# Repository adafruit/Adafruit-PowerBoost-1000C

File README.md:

## Adafruit PowerBoost 1000C
<a href="http://www.adafruit.com/products/2465"><br/>
Click here to purchase one from the Adafruit shop</a>

PowerBoost 1000C is the perfect power supply for your portable project! With a built-in load-sharing battery charger circuit, you'll be able to keep your power-hungry project running even while recharging the battery! This little DC/DC boost converter module can be powered by any 3.7V LiIon/LiPoly battery, and convert the battery output to 5.2V DC for running your 5V projects.

If you dont need the 1A battery charger, smart load-sharing, or 1A iOS resistors, check out the Powerboost 500C

Like our popular 5V 1A USB wall adapter, we tweaked the output to be 5.2V instead of a straight-up 5.0V so that there's a little bit of 'headroom' for long cables, high draw, the addition of a diode on the output if you wish, etc. The 5.2V is safe for all 5V-powered electronics like Arduino, Raspberry Pi, or Beagle Bone while preventing icky brown-outs during high current draw because of USB cable resistance.

The PowerBoost 1000C has at the heart a TPS61090 boost converter from TI. This boost converter chip has some really nice extras such as low battery detection, 2A internal switch, synchronous conversion, excellent efficiency, and 700KHz high-frequency operation. 

PCB files for Adafruit PowerBoost 1000C
-  https://www.adafruit.com/product/2465

### License

Adafruit invests time and resources providing this open source design, please support Adafruit and open-source hardware by purchasing products from [Adafruit](https://www.adafruit.com)!

All text above must be included in any redistribution

Designed by Limor Fried/Ladyada for Adafruit Industries.
Creative Commons Attribution/Share-Alike, all text above must be included in any redistribution. 
See license.txt for additional information.

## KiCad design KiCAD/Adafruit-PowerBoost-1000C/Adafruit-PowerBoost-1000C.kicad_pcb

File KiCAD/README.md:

!!! This project is port to KiCAD V5.99 and the PCB is not manufacured or tested, use KiCAD project files at your own risk.

This project is not an import to kicad from eagle, the schematic and layout are are created from scratch.

<br/>

<br/>

## Adafruit PowerBoost 1000C

<a href="http://www.adafruit.com/products/2465"><br/>
Click here to purchase one from the Adafruit shop</a>

PowerBoost 1000C is the perfect power supply for your portable project! With a built-in load-sharing battery charger circuit, you'll be able to keep your power-hungry project running even while recharging the battery! This little DC/DC boost converter module can be powered by any 3.7V LiIon/LiPoly battery, and convert the battery output to 5.2V DC for running your 5V projects.

If you dont need the 1A battery charger, smart load-sharing, or 1A iOS resistors, check out the Powerboost 500C

Like our popular 5V 1A USB wall adapter, we tweaked the output to be 5.2V instead of a straight-up 5.0V so that there's a little bit of 'headroom' for long cables, high draw, the addition of a diode on the output if you wish, etc. The 5.2V is safe for all 5V-powered electronics like Arduino, Raspberry Pi, or Beagle Bone while preventing icky brown-outs during high current draw because of USB cable resistance.

The PowerBoost 1000C has at the heart a TPS61090 boost converter from TI. This boost converter chip has some really nice extras such as low battery detection, 2A internal switch, synchronous conversion, excellent efficiency, and 700KHz high-frequency operation. 

PCB files for Adafruit PowerBoost 1000C
-  https://www.adafruit.com/product/2465

### License

Adafruit invests time and resources providing this open source design, please support Adafruit and open-source hardware by purchasing products from [Adafruit](https://www.adafruit.com)!

All text above must be included in any redistribution

Designed by Limor Fried/Ladyada for Adafruit Industries.
Creative Commons Attribution/Share-Alike, all text above must be included in any redistribution. 
See license.txt for additional information.

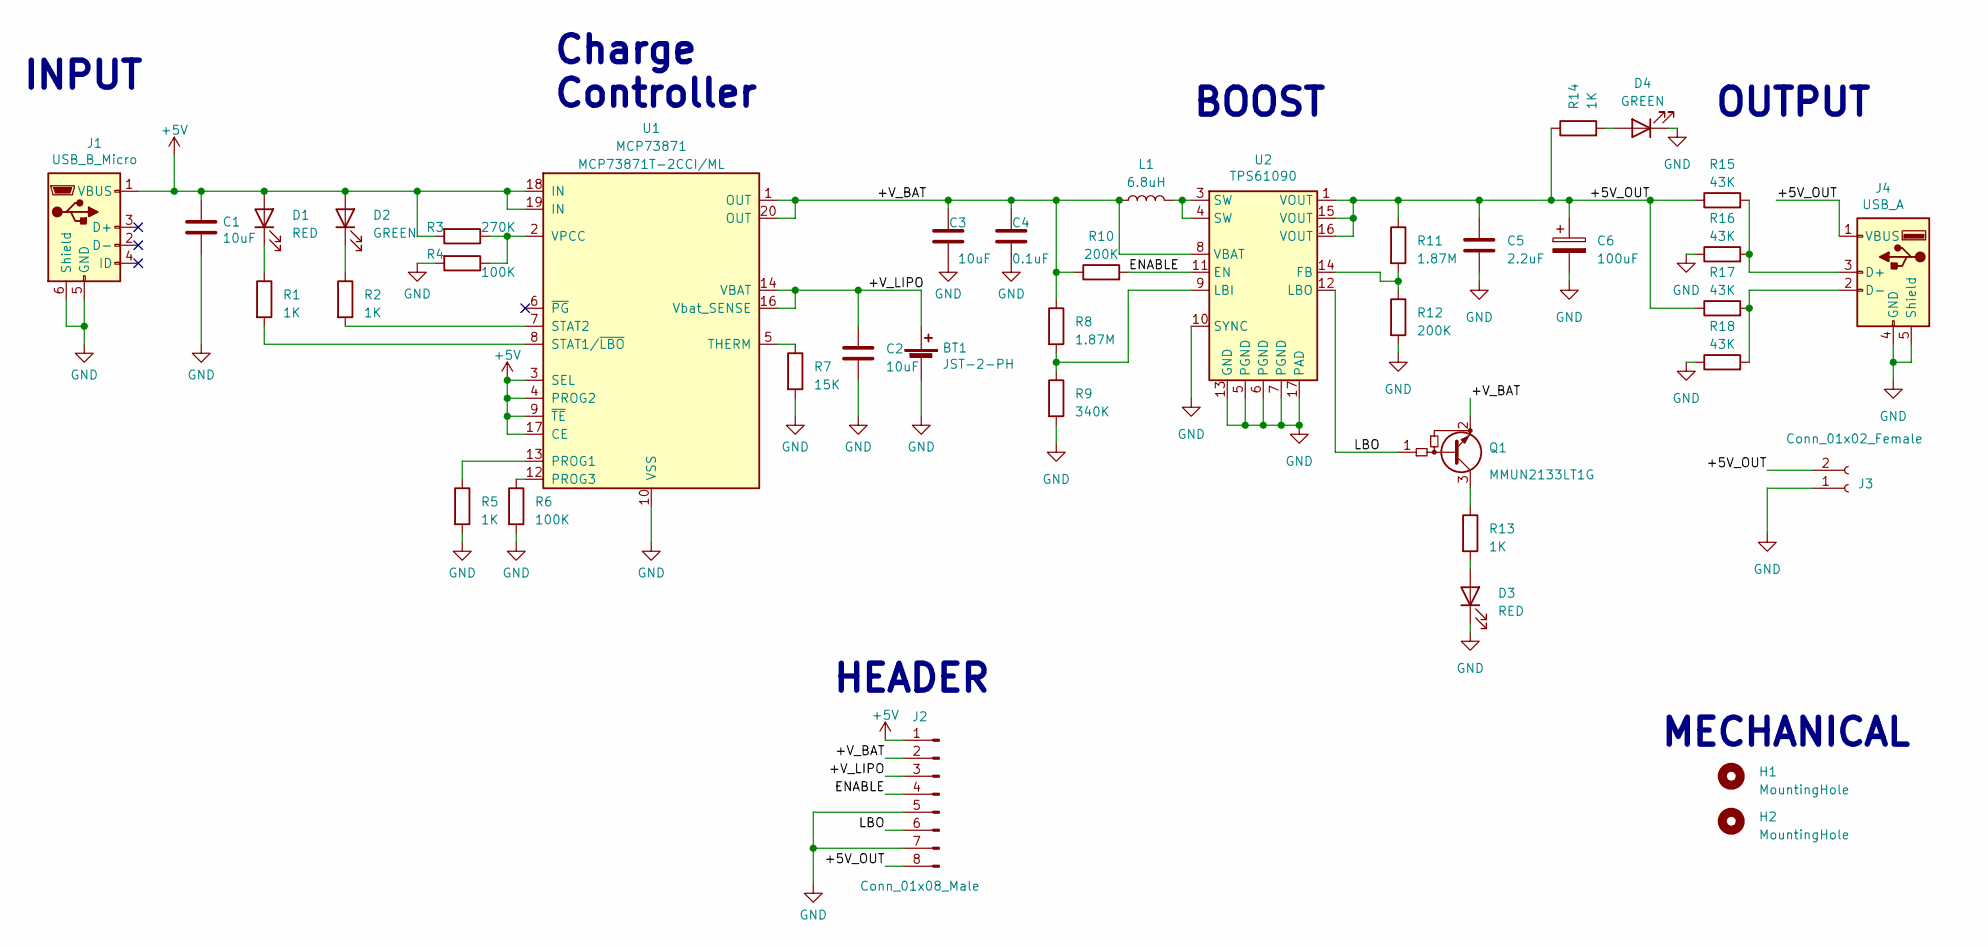
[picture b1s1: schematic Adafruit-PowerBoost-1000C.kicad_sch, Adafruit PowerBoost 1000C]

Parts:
BT1: JST-2-PH; JST_PH_S2B-PH-K_1x02_P2.00mm_Horizontal
C1, C2, C3: 10uF; C_0805_2012Metric
C4: 0.1uF; C_0805_2012Metric
C5: 2.2uF; C_0805_2012Metric
C6: 100uF; C_1210_3225Metric
D1, D3: RED; LED_0805_2012Metric
D2, D4: GREEN; LED_0805_2012Metric
H1, H2: MountingHole; MountingHole_2.5mm_Pad
J1: USB_B_Micro; USB_Micro-B_Wuerth_629105150521
J2: Conn_01x08_Male; PinHeader_1x08_P2.54mm_Vertical
J3: Conn_01x02_Female; JST_PH_S2B-PH-K_1x02_P2.00mm_Horizontal
J4: USB_A; USB_A_CONNFLY_DS1095-WNR0
L1: 6.8uH; IND_VLC5045
Q1: MMUN2133LT1G; SOT-23
R1, R2, R5, R13, R14: 1K; R_0805_2012Metric
R3: 270K; R_0805_2012Metric
R4, R6: 100K; R_0805_2012Metric
R7: 15K; R_0805_2012Metric
R8, R11: 1.87M; R_0805_2012Metric
R9: 340K; R_0805_2012Metric
R10, R12: 200K; R_0805_2012Metric
R15, R16, R17, R18: 43K; R_0805_2012Metric
U1: MCP73871; QFN-20-1EP_4x4mm_P0.5mm_EP2.5x2.5mm
U2: TPS61090; Texas_S-PVQFN-N16_EP2.7x2.7mm_ThermalVias

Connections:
+5V: C1.1, D1.2 (A), D2.2 (A), J1.1 (VBUS), J2.1, R3.2, U1.3 (SEL), U1.4 (PROG2), U1.9 (~TE), U1.17 (CE), U1.18 (IN), U1.19 (IN)
/+5V_OUT: C5.1, C6.1, J2.8, J3.2, J4.1 (VBUS), R11.1, R14.1, R15.1, R17.1, U2.1 (VOUT), U2.15 (VOUT), U2.16 (VOUT)
/+V_BAT: C3.1, C4.1, J2.2, L1.1, Q1.2 (E), R8.1, R10.1, U1.1 (OUT), U1.20 (OUT), U2.8 (VBAT)
/+V_LIPO: BT1.1 (+), C2.1, J2.3, U1.14 (VBAT), U1.15 (VBAT), U1.16 (Vbat_SENSE)
/ENABLE: J2.4, R10.2, U2.11 (EN)
/LBO: J2.6, Q1.1 (B), U2.12 (LBO)
GND: BT1.2 (-), C1.2, C2.2, C3.2, C4.2, C5.2, C6.2, D3.1 (K), D4.1 (K), J1.5 (GND), J1.6 (Shield), J2.5, J2.7, J3.1, J4.4 (GND), J4.5 (Shield), R4.2, R5.2, R6.2, R7.2, R9.2, R12.2, R16.1, R18.1, U1.10 (VSS), U1.11 (VSS), U1.21 (VSS), U2.5 (PGND), U2.6 (PGND), U2.7 (PGND), U2.10 (SYNC), U2.13 (GND), U2.17 (PAD)
unnamed: D1.1 (K), R1.1
unnamed: D2.1 (K), R2.1
unnamed: D3.2 (A), R13.2
unnamed: D4.2 (A), R14.2
unnamed: J4.2 (D-), R17.2, R18.2
unnamed: J4.3 (D+), R15.2, R16.2
unnamed: L1.2, U2.3 (SW), U2.4 (SW)
unnamed: Q1.3 (C), R13.1
unnamed: R1.2, U1.8 (STAT1/~LBO~)
unnamed: R2.2, U1.7 (STAT2)
unnamed: R3.1, R4.1, U1.2 (VPCC)
unnamed: R5.1, U1.13 (PROG1)
unnamed: R6.1, U1.12 (PROG3)
unnamed: R7.1, U1.5 (THERM)
unnamed: R8.2, R9.1, U2.9 (LBI)
unnamed: R11.2, R12.1, U2.14 (FB)

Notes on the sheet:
INPUT
Charge Controller
HEADER
BOOST
MECHANICAL
OUTPUT

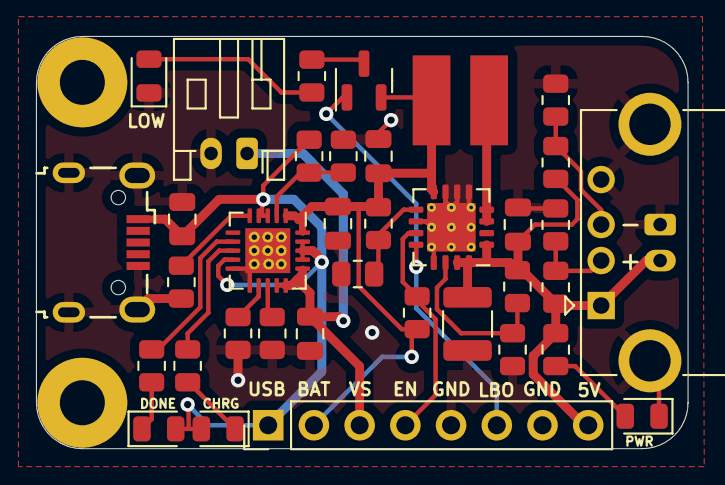
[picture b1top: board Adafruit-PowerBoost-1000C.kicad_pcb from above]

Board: 2 copper layers, 36.2 x 22.9 mm, 39 parts (1 on the bottom side), 23 nets.

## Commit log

2015-08-14 init
2021-06-19 Adds finshed KiCAD project
2021-06-19 Adds PDF schmeatic
